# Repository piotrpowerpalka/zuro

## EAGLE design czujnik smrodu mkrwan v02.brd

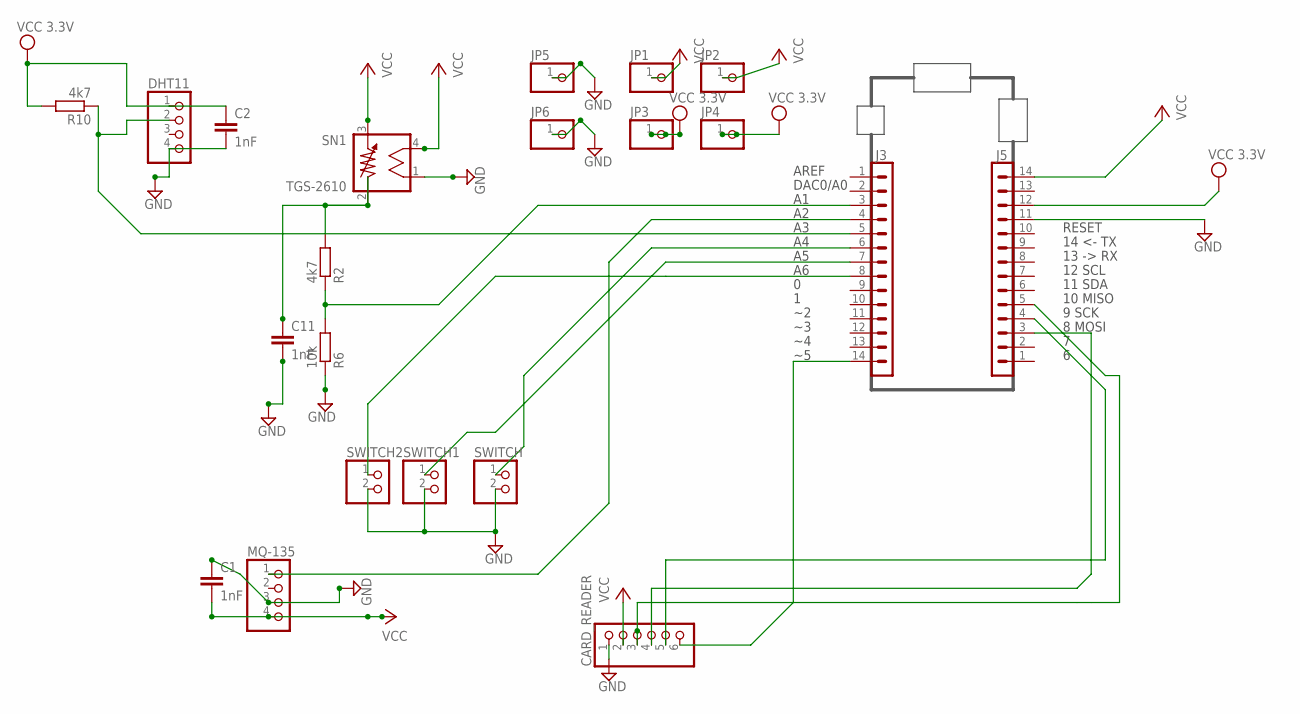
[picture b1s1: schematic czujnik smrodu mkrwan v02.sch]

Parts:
C1, C2, C11: 1nF; C2.5-3
CARD_READER: PINHD-1X6; 1X06
DHT11: PINHD-1X4; 1X04
J3, J5: DNP; 1X14_SMD_TH
JP1, JP2, JP3, JP4, JP5, JP6: PINHD-1X1; 1X01
MQ-135: PINHD-1X4; 1X04
R2, R10: 4k7; 0207/10
R6: 10k; 0207/10
SN1: TGS-2610
SWITCH, SWITCH1, SWITCH2: PINHD-1X2; 1X02

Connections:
GND: C1.1, C2.2, C11.2, CARD_READER.1, DHT11.4, J5.11, JP5.1, JP6.1, MQ-135.3, R6.1, SN1.1, SWITCH.2, SWITCH1.2, SWITCH2.2
unnamed: CARD_READER.3, J5.5
unnamed: CARD_READER.4, J5.3
unnamed: CARD_READER.5, J5.4
PA04_AIN4: DHT11.2, J3.5, R10.1
PA05_AIN5: J3.6, SWITCH.1
PA06_AIN6: J3.7, SWITCH1.1
PA07_AIN7: J3.8, SWITCH2.1
PB02_AIN10: J3.3, R2.1, R6.2
PB03_AIN11: J3.4, MQ-135.1
PB11_TCC0-W5: CARD_READER.6, J3.14
TGS2603_AIN: C11.1, R2.2, SN1.2
VCC: C1.2, C2.1, CARD_READER.2, DHT11.1, J5.12, J5.14, JP1.1, JP2.1, JP3.1, JP4.1, MQ-135.4, R10.2, SN1.3, SN1.4

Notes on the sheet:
14 <- TX
13 -> RX
12 SCL
RESET
11 SDA
8 MOSI
9 SCK
10 MISO
AREF
DAC0/A0

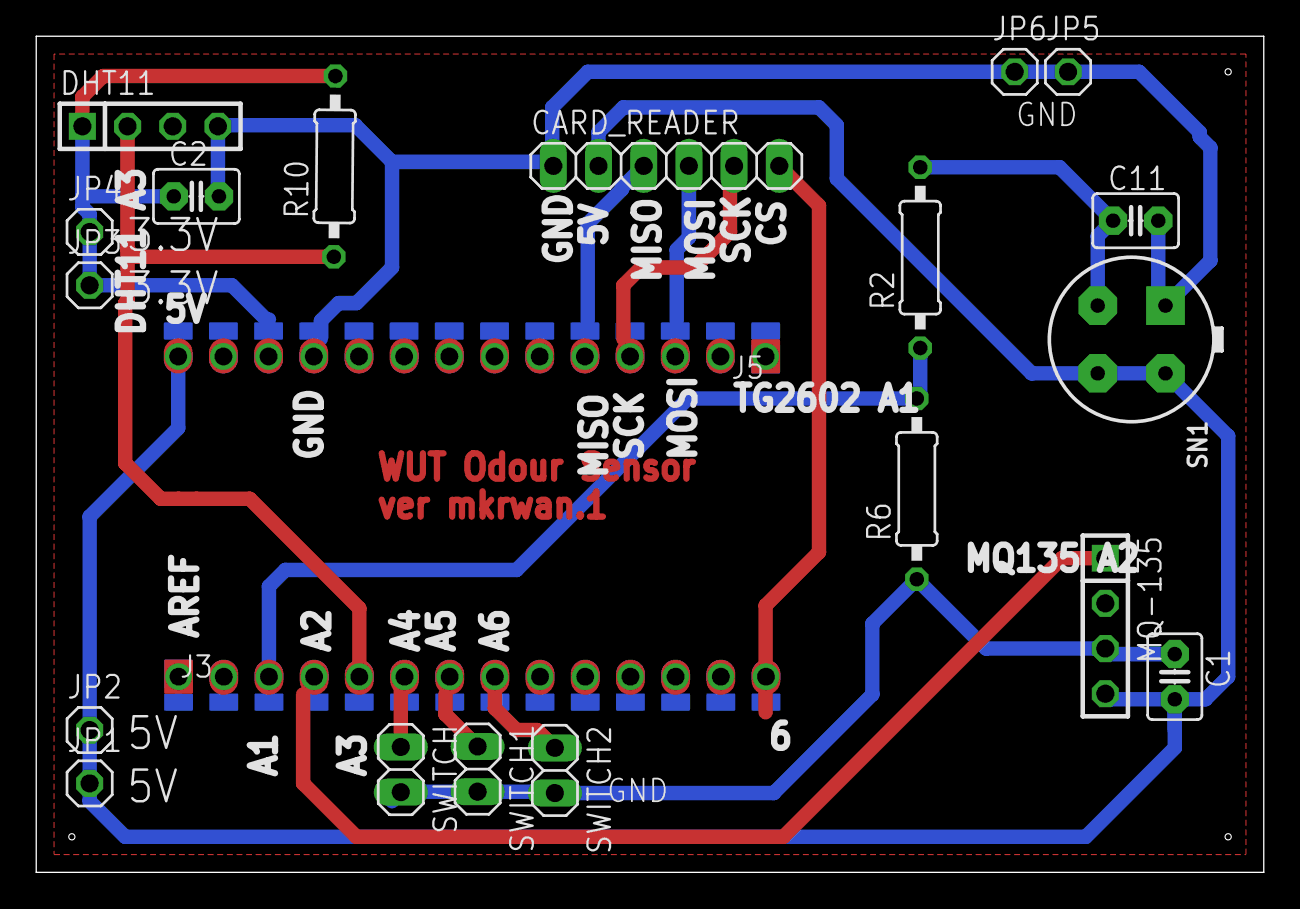
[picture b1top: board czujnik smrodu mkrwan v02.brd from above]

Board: 2 copper layers, 69.0 x 47.0 mm, 21 parts (0 on the bottom side), 13 nets.
